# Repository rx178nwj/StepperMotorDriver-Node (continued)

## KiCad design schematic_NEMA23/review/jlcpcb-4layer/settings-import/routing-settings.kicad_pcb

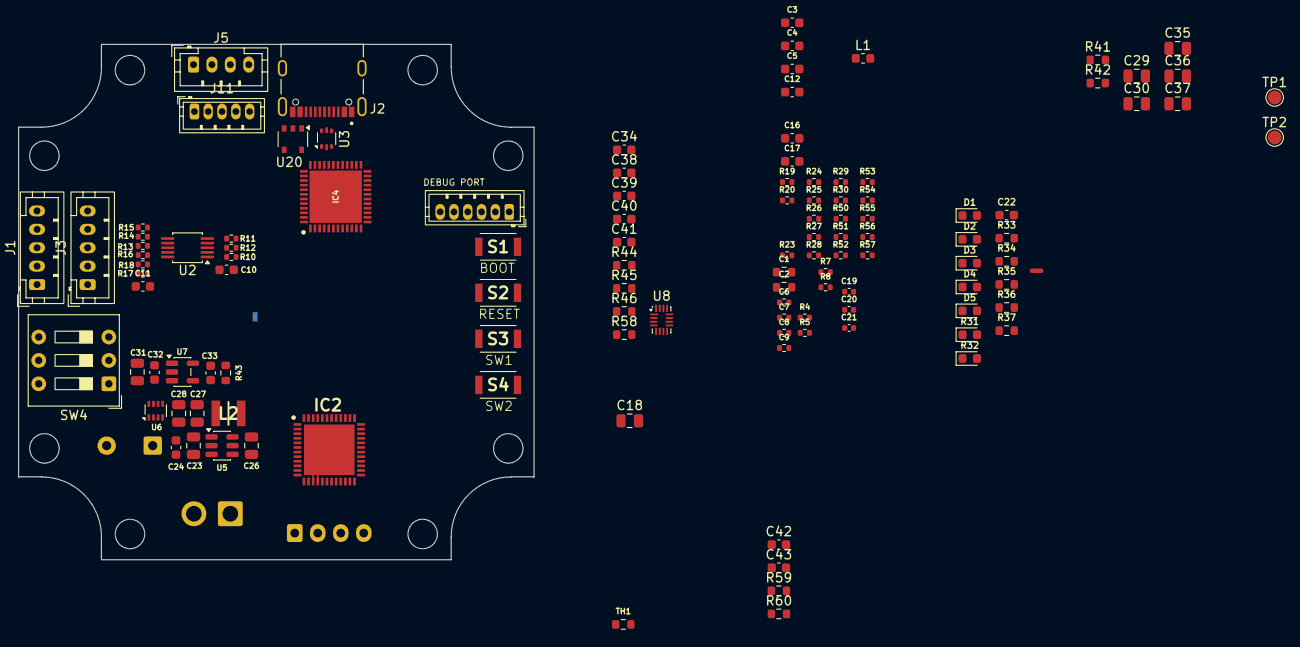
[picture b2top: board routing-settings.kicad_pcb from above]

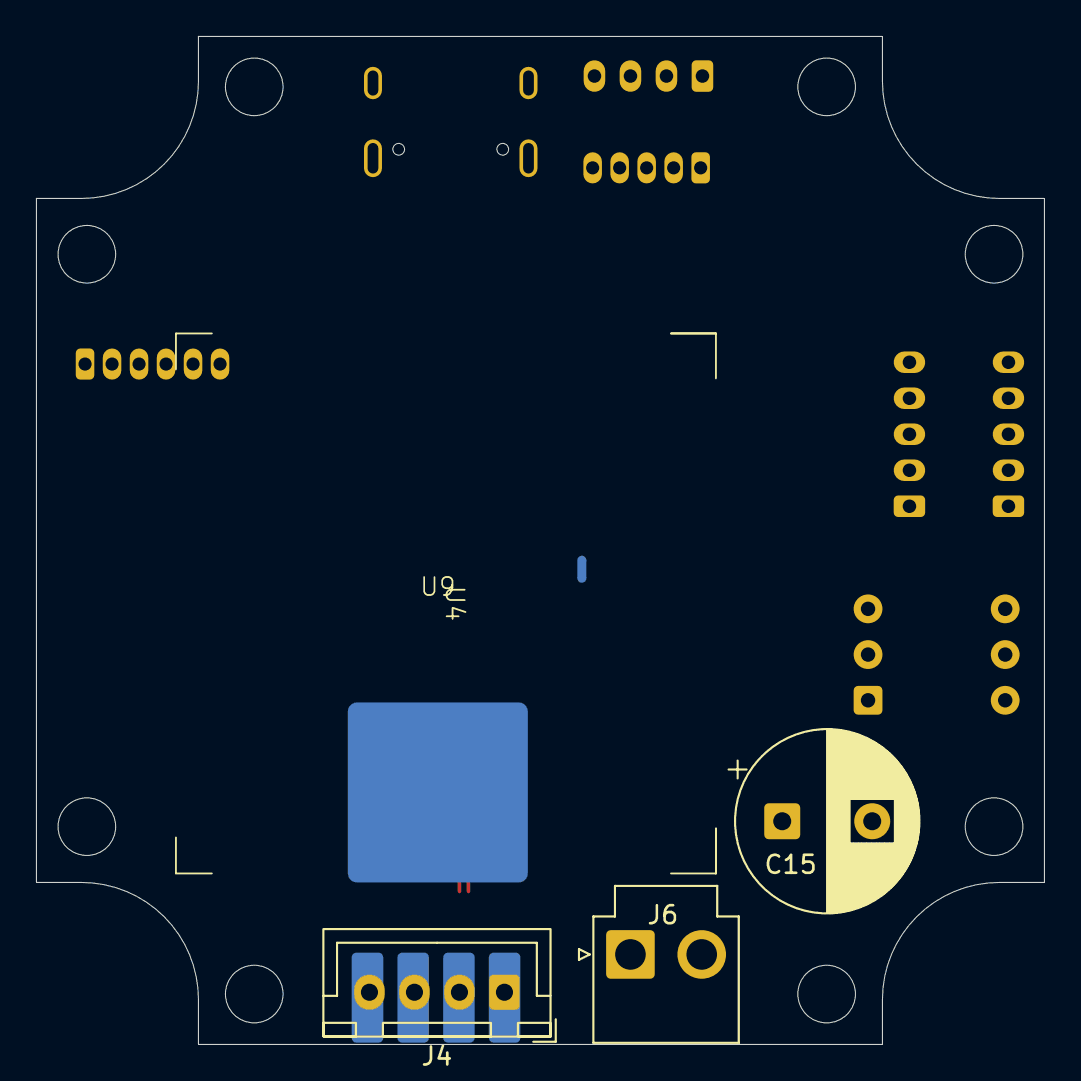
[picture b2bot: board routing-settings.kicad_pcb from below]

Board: 4 copper layers, 56.0 x 56.0 mm, 125 parts (7 on the bottom side), 78 nets.

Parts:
C1, C2: 0.1uF; R_0603_1608Metric
C3: 4.7uF; C_0603_1608Metric
C4: 2.2uF; C_0603_1608Metric
C5, C10, C11: 0.1uF; C_0603_1608Metric
C6, C7, C8, C9: 0.1uF; R_0402_1005Metric
C12, C22: 100nF; C_0603_1608Metric
C15: 220uF 63V low ESR; CP_Radial_D10.0mm_P5.00mm
C16, C17: 100nF 100V X7R; C_0603_1608Metric
C18: 10uF 50V X7R; C_0805_2012Metric
C19, C21: 100nF 16V X7R; C_0402_1005Metric
C20: 270pF C0G; C_0402_1005Metric
C23: 10uF/50V X7R; C_0805_2012Metric
C24: 100nF/100V; C_0603_1608Metric
C26, C29, C30, C35, C36, C37: 100nF/16V; C_0805_2012Metric
C27, C28: 22uF/16V; C_0805_2012Metric
C31: 10uF/16V; C_0805_2012Metric
C32, C33, C40: 1uF/16V; C_0603_1608Metric
C34, C38, C41: 100nF/16V; C_0603_1608Metric
C39: 10nF/16V; C_0603_1608Metric
C42, C43: 1uF; C_0603_1608Metric
D1, D2, D3, D4, D5: LED; LED_0603_1608Metric
IC2: TB67S249FTG,EL; QFN50P700X700X100-49N-D
IC4: STM32L433CCU6; QFN50P700X700X60-49N-D
J1, J3: Conn_01x05; JST_PH_B5B-PH-K_1x05_P2.00mm_Vertical
J2: 5077CR-16SMC2-BK-TR; NELTRON_5077CR-16SMC2-BK-TR
J4: MOTOR A+/A-/B-/B+; JST_XH_B4B-XH-A_1x04_P2.50mm_Vertical
J5: SENS I2C (3V3/GND/SCL/SDA); JST_PH_B4B-PH-K_1x04_P2.00mm_Vertical
J6: POWER 12-24V / >=10A (1=VIN,2=PGND); JST_VH_B2P-VH_1x02_P3.96mm_Vertical
J7: MOTOR A+/A-/B-/B+; 名称未設定_1
J8: SWD / SWO; JST_ZH_B6B-ZR_1x06_P1.50mm_Vertical
J11: Conn_01x05; JST_ZH_B5B-ZR_1x05_P1.50mm_Vertical
L1: Ferrite 600R@100MHz / >=200mA; L_0603_1608Metric
L2: 4.7uH / >=3.5A; DFE322520FD1R0MP2
NT1, NT2: PGND-GND STAR; NetTie-2_SMD_Pad0.5mm
R4, R5, R8, R12: 10k; R_0402_1005Metric
R7, R10, R11: 4.7k; R_0402_1005Metric
R13, R15, R16, R18: 600/DNP; R_0402_1005Metric
R14, R17: 120/DNP; R_0402_1005Metric
R19, R20, R23: 5.1k 1%; R_0402_1005Metric
R24, R52, R54, R56: 100k 1%; R_0402_1005Metric
R25, R26, R27, R28, R29: 10k 1%; R_0402_1005Metric
R30: 9.1k 1%; R_0402_1005Metric
R31, R32: 4.7k; LED_0603_1608Metric
R33, R34, R35, R37: 1k; R_0603_1608Metric
R36: 3.3k; R_0603_1608Metric
R41: 100k 1%; R_0603_1608Metric
R42: 30.1k 1%; R_0603_1608Metric
R43: 10k 1%; R_0603_1608Metric
R44: 180k 0.1%; R_0603_1608Metric
R45: 10k 0.1%; R_0603_1608Metric
R46: 4.7k; R_0603_1608Metric
R50: 0; R_0402_1005Metric
R51, R53, R55, R57: DNP; R_0402_1005Metric
R58, R59, R60: 10k; R_0603_1608Metric
S1, S2, S3, S4: SKRKAEE020
SW4: KSD32; SW_DIP_SPSTx03_Slide_9.78x9.8mm_W7.62mm_P2.54mm
TH1: Thermistor_NTC; R_0603_1608Metric
TP1, TP2: TestPoint; TestPoint_Pad_D1.5mm
U1: MainBoard
U2: PCA9615DP; TSSOP-10_3x3mm_P0.5mm
U3: USBLC6-2P6; SOT-666
U4: ヒートシンク30x30
U5: AP63205WU; TSOT-23-6
U6: TPS2116DRLR; SOT-583-8
U7: AP2112K-3.3TRG1; SOT-23-5
U8: TMUX1511RSVR; UQFN-16_1.8x2.6mm_P0.4mm
U9: サーマルパッド
U20: NCP360; TSOP-5_1.65x3.05mm_P0.95mm

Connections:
+3V3: C1.1, C2.1, C3.1, C10.1, C22.1, C33.1, C35.1, C36.1, C37.1, C38.1, C40.1, C41.1, IC4.1 (VBAT), IC4.24 (VDD_1), IC4.36 (VDDUSB), IC4.48 (VDD_2), J5.1, J8.1, J11.1, L1.2, R4.1, R5.1, R7.1, R10.1, R11.1, R12.1, R26.1, R27.1, R28.1, R31.1, R32.1, R43.1, S1.2, SW4.4, SW4.5, SW4.6, U2.1 (V_{DD(A)}), U7.5 (VOUT), U8.1 (SEL1), U8.16 (VDD)
/+5V: C11.1, C31.1, C32.1, R13.1, R16.1, U2.10 (V_{DD(B)}), U6.2 (VOUT), U6.7 (VOUT), U7.1 (VIN), U7.3 (EN)
/+5V_EXT: C27.1, C28.1, C29.1, L2.2, R41.1, U5.1 (FB), U6.3 (VIN1), U6.5 (MODE)
/ADDR0: IC4.5 (PH0-OSC_IN_(PH0)), R59.1, SW4.1
/ADDR1: IC4.6 (PH1-OSC_OUT_(PH1)), R60.1, SW4.2
/ADDR2: IC4.2 (PC13), R58.1, SW4.3
/AD_IN: IC4.17 (PA7), J11.5
/BUCK_BOOT: C26.1, U5.6 (BST)
/BUCK_SW: C26.2, L2.1, U5.5 (SW)
/DAC_VREF: IC4.14 (PA4), R29.2
/DI2C_SCL_M: J1.4, J3.4, R14.2, R15.1, U2.6 (DSCLM)
/DI2C_SCL_P: J1.3, J3.3, R13.2, R14.1, U2.7 (DSCLP)
/DI2C_SDA_M: J1.2, J3.2, R17.2, R18.1, U2.9 (DSDAM)
/DI2C_SDA_P: J1.1, J3.1, R16.2, R17.1, U2.8 (DSDAP)
/DRV_AGC0: IC2.1 (AGC0), IC4.45 (PB8)
/DRV_AGC1: IC2.2 (AGC1), IC4.46 (PB9)
/DRV_BOOST: IC2.6 (BOOST), R54.2, R55.1
/DRV_CLIM0: IC2.3 (CLIM0), R50.2, R51.1
/DRV_CLIM1: IC2.4 (CLIM1), R52.2, R53.1
/DRV_CLK: IC2.43 (CLK), IC4.29 (PA8)
/DRV_DIR: IC2.42 (CW/CCW), IC4.30 (PA9)
/DRV_DMODE0: IC2.39 (DMODE0), IC4.25 (PB12)
/DRV_DMODE1: IC2.40 (DMODE1), IC4.26 (PB13)
/DRV_DMODE2: IC2.41 (DMODE2), IC4.27 (PB14)
/DRV_EN: IC2.44 (ENABLE), IC4.31 (PA10), R25.1
/DRV_FLIM: IC2.5 (FLIM), R56.2, R57.1
/DRV_LO1: IC2.47 (LO1), IC4.12 (PA2), R26.2
/DRV_LO2: IC2.48 (LO2), IC4.13 (PA3), R27.2
/DRV_LTH: IC2.7 (LTH), R24.1
/DRV_MO: IC2.46 (MO), IC4.4 (PC15-OSC32_OUT_(PC15)), R28.2
/DRV_OSCM: C20.1, IC2.35 (OSCM), R23.2
/DRV_RESET: IC2.45 (RESET), IC4.28 (PB15)
/DRV_VCC: C19.1, IC2.33 (VCC_1), IC2.34 (VCC_2), R23.1, R50.1, R52.1, R54.1, R56.1
/DRV_VREF: C21.1, IC2.31 (VREFB), IC2.32 (VREFA), R29.1, R30.1, TP2.1 (1_1)
/ENC_A_HOME1: IC4.38 (PA15_(JTDI)), J11.3
/ENC_B_HOME2: IC4.11 (PA1), J11.4
/I2C_PC_SCL: IC4.21 (PB10), R11.2, U2.4 (SCL)
/I2C_PC_SDA: IC4.22 (PB11), R10.2, U2.2 (SDA)
/I2C_SENS_SCL: IC4.42 (PB6), J5.3, R31.2
/I2C_SENS_SDA: IC4.43 (PB7), J5.4, R32.2
/LED_COMM: IC4.19 (PB1), R37.1
/LED_FAULT: IC4.20 (PB2), R34.1
/LED_MCU: IC4.18 (PB0), R35.1
/LED_RUN: IC4.15 (PA5), R33.1
/NRST: C6.1, IC4.7 (NRST), J8.5, S2.1
/OUTA_N: IC2.17 (OUTA-_1), IC2.18 (OUTA-_2), J4.2, J7.2
/OUTA_P: IC2.13 (OUTA+_1), IC2.14 (OUTA+_2), J4.1, J7.1
/OUTB_N: IC2.19 (OUTB-_1), IC2.20 (OUTB-_2), J4.3, J7.3
/OUTB_P: IC2.23 (OUTB+_1), IC2.24 (OUTB+_2), J4.4, J7.4
/PB8_BOOT: IC4.44 (PH3-BOOT0), R8.1, S1.1
/PCA9615_EN: R12.2, U2.3 (EN)
/POWER_PR1: R41.2, R42.1, U6.4 (PR1)
/PWR_ST: IC4.3 (PC14-OSC32_IN_(PC14)), R43.2, U6.8 (ST)
/SWCLK: IC4.37 (PA14_(JTCK-SWCLK)), J8.4
/SWDIO: IC4.34 (PA13_(JTMS-SWDIO)), J8.2
/SWITCH1: C7.1, IC4.40 (PB4_(NJTRST)), R4.2, S3.1
/SWITCH2: C8.1, IC4.41 (PB5), R5.2, S4.1
/SWO: IC4.39 (PB3_(JTDO-TRACESWO)), J8.6
/TEMP: C9.1, IC4.16 (PA6), R7.2, TH1.1
/USB_CC1: J2.A5 (CC1), R19.1
/USB_CC2: J2.B5 (CC2), R20.1
/USB_PC_DM: IC4.32 (PA11), J2.A7 (DN1), J2.B7 (DN2), U3.3 (I/O2), U3.4 (I/O2)
/USB_PC_DP: IC4.33 (PA12), J2.A6 (DP1), J2.B6 (DP2), U3.1 (I/O1), U3.6 (I/O1)
/USB_VBUS: C12.1, C30.1, C43.1, U3.5 (VBUS), U6.6 (VIN2), U20.5 (OUT)
/USB_VBUS_SRC: C42.1, J2.A4_B9 (VBUS), J2.B4_A9 (VBUS), U20.1 (IN)
/VDDA: C4.1, C5.1, C39.1, IC4.9 (VDDA/VREF+), L1.1
/VM: C15.1, C16.1, C17.1, C18.1, C23.1, C24.1, IC2.10 (VMA_1), IC2.11 (VMA_2), IC2.26 (VMB_1), IC2.27 (VMB_2), J6.1, R36.1, R44.1, TP1.1 (1_1), U5.2 (EN), U5.3 (IN)
/VM_DIV: R44.2, R45.1, U8.2 (S1)
/VM_SENSE: C34.1, IC4.10 (PA0), R46.2
/VM_SENSE_ISO: R46.1, U8.3 (D1)
GND: C1.2, C2.2, C3.2, C6.2, C7.2, C8.2, C9.2, C10.2, C11.2, C12.2, C19.2, C20.2, C21.2, C22.2, C23.2, C24.2, C27.2, C28.2, C29.2, C30.2, C31.2, C32.2, C33.2, C35.2, C36.2, C37.2, C38.2, C40.2, C41.2, C42.2, C43.2, D1.1 (K), D2.1 (K), D3.1 (K), D5.1 (K), IC2.8 (GND_1), IC2.29 (GND_2), IC2.30 (GND_3), IC4.23 (VSS_1), IC4.35 (VSS_2), IC4.47 (VSS_3), IC4.49 (EP), J1.5, J2.A1_B12 (GND), J2.B1_A12 (GND), J2.S1 (SHIELD), J2.S2 (SHIELD), J2.S3 (SHIELD), J2.S4 (SHIELD), J3.5, J5.2, J8.3, J11.2, NT1.2, NT2.1, R8.2, R15.2, R18.2, R19.2, R20.2, R24.2, R25.2, R30.2, R42.2, R51.2, R53.2, R55.2, R57.2, R58.2, R59.2, R60.2, S2.2, S3.2, S4.2, TH1.2, U2.5 (V_{SS}), U3.2 (GND), U5.4 (GND), U6.1 (GND), U7.2 (GND), U8.4 (SEL2), U8.5 (S2), U8.8 (GND), U8.10 (S3), U8.11 (SEL3), U8.14 (S4), U8.15 (SEL4), U20.2 (GND), U20.3 (~EN)
GNDA: C4.2, C5.2, C34.2, C39.2, IC4.8 (VSSA/VREF-), NT2.2, R45.2
GNDPWR: C15.2, C16.2, C17.2, C18.2, D4.1 (K), IC2.15 (RSAGND_1), IC2.16 (RSAGND_2), IC2.21 (RSBGND_1), IC2.22 (RSBGND_2), IC2.49 (EP), J6.2, NT1.1, U9.EP (EP_EP)
unnamed: D1.2 (A), R33.2
unnamed: D2.2 (A), R34.2
unnamed: D3.2 (A), R35.2
unnamed: D4.2 (A), R36.2
unnamed: D5.2 (A), R37.2

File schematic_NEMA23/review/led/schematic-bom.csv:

"Refs","Value","Footprint","Qty","DNP"
"C1","0.1uF","Resistor_SMD:R_0603_1608Metric","1",""
"C2","0.1uF","Resistor_SMD:R_0603_1608Metric","1",""
"C3","4.7uF","Capacitor_SMD:C_0603_1608Metric","1",""
"C4","2.2uF","Capacitor_SMD:C_0603_1608Metric","1",""
"C5","0.1uF","Capacitor_SMD:C_0603_1608Metric","1",""
"C6","0.1uF","Resistor_SMD:R_0402_1005Metric","1",""
"C7","0.1uF","Resistor_SMD:R_0402_1005Metric","1",""
"C8","0.1uF","Resistor_SMD:R_0402_1005Metric","1",""
"C9","0.1uF","Resistor_SMD:R_0402_1005Metric","1",""
"C10","0.1uF","Capacitor_SMD:C_0603_1608Metric","1",""
"C11","0.1uF","Capacitor_SMD:C_0603_1608Metric","1",""
"C12","100nF","Capacitor_SMD:C_0603_1608Metric","1",""
"C13","1uF","Capacitor_SMD:C_0603_1608Metric","1",""
"C14","100nF","Capacitor_SMD:C_0402_1005Metric","1",""
"C15","220uF 63V low ESR","Capacitor_THT:CP_Radial_D10.0mm_P5.00mm","1",""
"C16","100nF 100V X7R","Capacitor_SMD:C_0603_1608Metric","1",""
"C17","100nF 100V X7R","Capacitor_SMD:C_0603_1608Metric","1",""
"C18","10uF 50V X7R","Capacitor_SMD:C_0805_2012Metric","1",""
"C19","100nF 16V X7R","Capacitor_SMD:C_0402_1005Metric","1",""
"C20","270pF C0G","Capacitor_SMD:C_0402_1005Metric","1",""
"C21","100nF 16V X7R","Capacitor_SMD:C_0402_1005Metric","1",""
"C22","100nF","Capacitor_SMD:C_0603_1608Metric","1",""
"D1","LED","LED_SMD:LED_0603_1608Metric","1",""
"D2","LED","LED_SMD:LED_0603_1608Metric","1",""
"D4","LED","LED_SMD:LED_0603_1608Metric","1",""
"IC2","TB67S249FTG,EL","Library:QFN50P700X700X100-49N-D","1",""
"IC4","STM32L433CCU6","Library:QFN50P700X700X60-49N-D","1",""
"J1","Conn_01x06","Connector_JST:JST_PH_B5B-PH-K_1x05_P2.00mm_Vertical","1",""
"J2","5077CR-16SMC2-BK-TR","Library:NELTRON_5077CR-16SMC2-BK-TR","1",""
"J3","Conn_01x06","Connector_JST:JST_PH_B5B-PH-K_1x05_P2.00mm_Vertical","1",""
"J4","MOTOR A+/A-/B+/B-","Connector_JST:JST_XH_B4B-XH-A_1x04_P2.50mm_Vertical","1",""
"J5","SENS I2C (3V3/GND/SCL/SDA)","Connector_JST:JST_PH_B4B-PH-K_1x04_P2.00mm_Vertical","1",""
"L1","L","LED_SMD:LED_0201_0603Metric_Pad0.64x0.40mm_HandSolder","1",""
"NT1","PGND-GND STAR","NetTie:NetTie-2_SMD_Pad0.5mm","1",""
"NT2","PGND-GND STAR","NetTie:NetTie-2_SMD_Pad0.5mm","1",""
"R1","10k","Resistor_SMD:R_0402_1005Metric","1",""
"R2","0","Resistor_SMD:R_0402_1005Metric","1",""
"R3","10k","Resistor_SMD:R_0402_1005Metric","1",""
"R4","10k","Resistor_SMD:R_0402_1005Metric","1",""
"R5","10k","Resistor_SMD:R_0402_1005Metric","1",""
"R6","10k","Resistor_SMD:R_0402_1005Metric","1",""
"R7","4.7k","Resistor_SMD:R_0402_1005Metric","1",""
"R8","10k","Resistor_SMD:R_0402_1005Metric","1",""
"R9","100k","Resistor_SMD:R_0402_1005Metric","1",""
"R10","4.7k","Resistor_SMD:R_0402_1005Metric","1",""
"R11","4.7k","Resistor_SMD:R_0402_1005Metric","1",""
"R12","10k","Resistor_SMD:R_0402_1005Metric","1",""
"R13","600/DNP","Resistor_SMD:R_0402_1005Metric","1",""
"R14","120/DNP","Resistor_SMD:R_0402_1005Metric","1",""
"R15","600/DNP","Resistor_SMD:R_0402_1005Metric","1",""
"R16","600/DNP","Resistor_SMD:R_0402_1005Metric","1",""
"R17","120/DNP","Resistor_SMD:R_0402_1005Metric","1",""
"R18","600/DNP","Resistor_SMD:R_0402_1005Metric","1",""
"R19","5.1k 1%","Resistor_SMD:R_0402_1005Metric","1",""
"R20","5.1k 1%","Resistor_SMD:R_0402_1005Metric","1",""
"R21","33k 1%","Resistor_SMD:R_0402_1005Metric","1",""
"R22","82k 1%","Resistor_SMD:R_0402_1005Metric","1",""
"R23","5.1k 1%","Resistor_SMD:R_0402_1005Metric","1",""
"R24","100k 1%","Resistor_SMD:R_0402_1005Metric","1",""
"R25","10k 1%","Resistor_SMD:R_0402_1005Metric","1",""
"R26","10k 1%","Resistor_SMD:R_0402_1005Metric","1",""
"R27","10k 1%","Resistor_SMD:R_0402_1005Metric","1",""
"R28","10k 1%","Resistor_SMD:R_0402_1005Metric","1",""
"R29","10k 1%","Resistor_SMD:R_0402_1005Metric","1",""
"R30","9.1k 1%","Resistor_SMD:R_0402_1005Metric","1",""
"R31","4.7k","LED_SMD:LED_0603_1608Metric","1",""
"R32","4.7k","LED_SMD:LED_0603_1608Metric","1",""
"R33","1k","Resistor_SMD:R_0603_1608Metric","1",""
"R34","1k","Resistor_SMD:R_0603_1608Metric","1",""
"R36","1k","Resistor_SMD:R_0603_1608Metric","1",""
"R50","0","Resistor_SMD:R_0402_1005Metric","1",""
"R51","DNP","Resistor_SMD:R_0402_1005Metric","1",""
"R52","100k 1%","Resistor_SMD:R_0402_1005Metric","1",""
"R53","DNP","Resistor_SMD:R_0402_1005Metric","1",""
"R54","100k 1%","Resistor_SMD:R_0402_1005Metric","1",""
"R55","DNP","Resistor_SMD:R_0402_1005Metric","1",""
"R56","100k 1%","Resistor_SMD:R_0402_1005Metric","1",""
"R57","DNP","Resistor_SMD:R_0402_1005Metric","1",""
"SW1","SW_MEC_5G","Library:ＴＶＡＦ０６－Ａ０２０Ｂ－Ｒ","1",""
"SW2","SW_MEC_5G","Library:ＴＶＡＦ０６－Ａ０２０Ｂ－Ｒ","1",""
"SW3","SW_MEC_5G","Library:ＴＶＡＦ０６－Ａ０２０Ｂ－Ｒ","1",""
"SW5","SW_MEC_5G","Library:ＴＶＡＦ０６－Ａ０２０Ｂ－Ｒ","1",""
"TH1","Thermistor_NTC","Resistor_SMD:R_0603_1608Metric","1",""
"U1","","Library:MainBoard","1",""
"U2","PCA9615DP","Package_SO:TSSOP-10_3x3mm_P0.5mm","1",""
"U3","USBLC6-2P6","Package_TO_SOT_SMD:SOT-666","1",""
"U4","","Library:ヒートシンク40x40","1",""

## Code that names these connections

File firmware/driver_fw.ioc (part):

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Mcu.Name=STM32L433C(B-C)Ux
Mcu.Package=UFQFPN48
Mcu.UserName=STM32L433CCUx
PA0.GPIOParameters=GPIO_Label
PA0.GPIO_Label=VM_SENSE
PA0.Signal=ADCx_IN5
PA10.GPIOParameters=GPIO_Label
PA10.GPIO_Label=DRV_EN
PA10.Signal=GPIO_Output
PA11.Mode=Device
PA11.Signal=USB_DM
PA12.Mode=Device
PA12.Signal=USB_DP
PA13\ (JTMS-SWDIO).Mode=Trace_Asynchronous_SW
PA13\ (JTMS-SWDIO).Signal=SYS_JTMS-SWDIO
PA14\ (JTCK-SWCLK).Mode=Trace_Asynchronous_SW
PA14\ (JTCK-SWCLK).Signal=SYS_JTCK-SWCLK
PA2.GPIOParameters=GPIO_Label,GPIO_ModeDefaultEXTI
PA2.GPIO_Label=DRV_LO1
PA2.GPIO_ModeDefaultEXTI=GPIO_MODE_IT_FALLING
PA2.Signal=GPXTI2
PA3.GPIOParameters=GPIO_Label,GPIO_ModeDefaultEXTI
PA3.GPIO_Label=DRV_LO2
PA3.GPIO_ModeDefaultEXTI=GPIO_MODE_IT_FALLING
PA3.Signal=GPXTI3
PA4.GPIOParameters=GPIO_Label
PA4.GPIO_Label=DAC_VREF
PA4.Signal=COMP_DAC11_group
PA5.GPIOParameters=GPIO_Label
PA5.GPIO_Label=LED_RUN
PA5.Signal=GPIO_Output
PA6.GPIOParameters=GPIO_Label
PA6.GPIO_Label=TEMP
PA6.Signal=ADCx_IN11
PA7.GPIOParameters=GPIO_Label
PA7.GPIO_Label=AD_IN
PA7.Signal=ADCx_IN12
PA8.GPIOParameters=GPIO_Label
PA8.GPIO_Label=DRV_CLK
PA8.Signal=S_TIM1_CH1
PA9.GPIOParameters=GPIO_Label
PA9.GPIO_Label=DRV_DIR
PA9.Signal=GPIO_Output
PB0.GPIOParameters=GPIO_Label
PB0.GPIO_Label=LED_MCU
PB0.Signal=GPIO_Output
PB1.GPIOParameters=GPIO_Label
PB1.GPIO_Label=LED_COMM
PB1.Signal=GPIO_Output
PB10.GPIOParameters=GPIO_Label
PB10.GPIO_Label=DRV_AGC0
PB10.Signal=GPIO_Output
PB11.GPIOParameters=GPIO_Label
PB11.GPIO_Label=DRV_AGC1
PB11.Signal=GPIO_Output
PB12.GPIOParameters=GPIO_Label
PB12.GPIO_Label=DRV_DMODE0
PB12.Signal=GPIO_Output
PB13.GPIOParameters=GPIO_Label
PB13.GPIO_Label=DRV_DMODE1
PB13.Signal=GPIO_Output
PB14.GPIOParameters=GPIO_Label
PB14.GPIO_Label=DRV_DMODE2
PB14.Signal=GPIO_Output
PB15.GPIOParameters=GPIO_Label
PB15.GPIO_Label=DRV_RESET
PB15.Signal=GPIO_Output
PB2.GPIOParameters=GPIO_Label
PB2.GPIO_Label=LED_FAULT
PB2.Signal=GPIO_Output
PB3\ (JTDO-TRACESWO).Mode=Trace_Asynchronous_SW
PB3\ (JTDO-TRACESWO).Signal=SYS_JTDO-SWO
PB4\ (NJTRST).GPIOParameters=GPIO_Label
PB4\ (NJTRST).GPIO_Label=SWITCH1
PB4\ (NJTRST).Signal=GPIO_Input
PB5.GPIOParameters=GPIO_Label
PB5.GPIO_Label=SWITCH2
PB5.Signal=GPIO_Input
PB6.GPIOParameters=GPIO_Label
PB6.GPIO_Label=I2C_SENS_SCL
PB6.Mode=I2C
PB6.Signal=I2C1_SCL
PB7.GPIOParameters=GPIO_Label
PB7.GPIO_Label=I2C_SENS_SDA
PB7.Mode=I2C
PB7.Signal=I2C1_SDA
PB8.GPIOParameters=GPIO_Label
PB8.GPIO_Label=CAN_RX
PB8.Mode=CAN_Activate
PB8.Signal=CAN1_RX
PB9.GPIOParameters=GPIO_Label
PB9.GPIO_Label=CAN_TX
PB9.Mode=CAN_Activate
PB9.Signal=CAN1_TX
PC13.GPIOParameters=GPIO_Label
PC13.GPIO_Label=ADDR2
PC13.Signal=GPIO_Input
PC14-OSC32_IN\ (PC14).GPIOParameters=GPIO_Label
PC14-OSC32_IN\ (PC14).GPIO_Label=PWR_ST
PC14-OSC32_IN\ (PC14).Signal=GPIO_Input
PC15-OSC32_OUT\ (PC15).GPIOParameters=PinState,GPIO_Label
PC15-OSC32_OUT\ (PC15).GPIO_Label=CAN_S
PC15-OSC32_OUT\ (PC15).PinState=GPIO_PIN_RESET
PC15-OSC32_OUT\ (PC15).Signal=GPIO_Output
PH0-OSC_IN\ (PH0).GPIOParameters=GPIO_Label
PH0-OSC_IN\ (PH0).GPIO_Label=ADDR0
PH0-OSC_IN\ (PH0).Signal=GPIO_Input
PH1-OSC_OUT\ (PH1).GPIOParameters=GPIO_Label
PH1-OSC_OUT\ (PH1).GPIO_Label=ADDR1
PH1-OSC_OUT\ (PH1).Signal=GPIO_Input
RCC.HSE_VALUE=8000000
RCC.SYSCLKFreq_VALUE=80000000
RCC.SYSCLKSource=RCC_SYSCLKSOURCE_PLLCLK
board=custom
